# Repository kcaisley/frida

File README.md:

# FRIDA: Fast radiation imaging digitizer array

Frame-based radiation detectors with integrating front-ends are especially well-suited for applications like electron microscopy and X-ray imaging where hit-rates are high, spatial resolution should be maximized with simple pixels, and energy resolution is needed, but particles need not be individually discriminated in time, space, or spectrum. In an experimental setting, fast frame rates allow for real time in-situ observations. Potential subjects include rapid chemical processes, molecular dynamics of proteins, crystal nucleation and growth, material phase transitions, thermal conductivity, charge transfer, and mechanical strain.

This project pursues the possibility of a single-reticle array larger than 1 Mpixel with a continuous frame-rate surpassing 100,000 fps. For the conjunction of these two specifications to be met, one must have a compact and power efficient bank of column-parallel data converters, which at 10-12 bit resolution churn out data at a rate in excess of 1000 Gbps. To fit within the constraints of a chip bottom, the converter fabric must respect a restricted metric of 1 W/cm^2 while exceeding a 5 ksps/µm^2 sampling rate density. Successive-approximation ADCs are identified as the optimal choice, and various topologies and techniques will be analyzed to meet our goals.

Research question: How do we best allocate the quantity and weighting of SA bit positions, in order to yeild the highest resolution (in ENOB) for a given power, area, and power budget, and with a given amount of power supply noise?

## Block diagram of example system

## Modeling and analysis workflow

## Past designs vs current target

| Design                  | EDET DCD    | CoRDIA     | pre-Helena | Helena      |
|-------------------------|-------------|------------|------------|-------------|
| ADC resolution          | 8-bit       | 10-bit     | 8-bit      | 10-bit      |
| Conversion rate         | 10 MHz      | 2.5MHz     | 5 MHz      | 10 MHz      |
| Area of one ADC         | 100x200 μm² | 80x330 μm² | 60x800 μm² | 20x100 μm²  |
| Power of one ADC        | 1800 μW     | 30 μW      | 700 μW     | 100 μW      |
| FOM_csa (conv/sec/area) | 500 Hz/μm²  | 95 Hz/μm²  | 105 Hz/μm² | 5000 Hz/μm² |
| FOM_epc (energy/conv)   | 180 pJ      | 12 pJ      | 155 pJ     | 10 pJ       |
| FOM_ppa (power/area)    | 9.0 W/cm²   | 0.11 W/cm² | 1.45 W/cm² | 5.0 W/cm²   |
| ADC qty Mpix @ 100 KHz  | 10000       | 40000      | 20000      | 10000       |
| ADCs total pixel rate   | 100 Gpx/s   | 100 Gpx/s  | 100 Gpx/s  | 100 Gpx/s   |
| ADCs total data rate    | 800 Gb/s    | 1 Tb/s     | 800 Gb/s   | 1 Tb/s      |
| ADCs total area         | 2.0 cm²     | 10.5 cm²   | 9.6 cm²    | 0.2 cm²     |
| ADCs total power        | 35.0 W      | 1.2 W      | 14 W       | 1.0 W       |

NOTE: EDET DCD 1800 μW seems high, does it erroneously includes input amp?

# Project organization (proposal)

```
├── src
├── hdl
├── oa  (Caeleste input collateral eventually to be deleted)
├── netlists (library of generic netlists, and Verilog A models -> converted with find+replace)
├── impl
│   └── tsmc65 (1. impl netlists/oa schems/layouts/ 2. pointers to )
│   └── tsmc28
├── sim
│   └── tsmc65 (runs against impl netlists, since we have to have to include external libs)
│   └── tsmc28
├── tech
│   └── tsmc65 (EDA env start dir)
│   └── tsmc28
├── writing
```

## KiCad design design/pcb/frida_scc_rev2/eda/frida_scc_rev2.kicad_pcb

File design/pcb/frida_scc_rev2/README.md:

# frida_scc_rev2

The FRIDA single-chip card, revision 2.0: the test board for the FRIDA-1 ADC, written in
[Zener](https://docs.pcb.new/pages/spec.md). The `.zen` files are the source; the `pcb` tool makes
the netlist, the KiCad schematic and the KiCad board from them. The previous board is
`../frida-scc-1p1.kicad_pro`.

This is a first sketch: it builds (236 components) and generates. The board has frida-scc-1p1's
outline, stack-up and, for the 92 parts both boards have, its placement; the 144 new parts are
placed around them. Routing is in progress, nothing is simulated yet, and the items under "Open
questions" are undecided.

## Flow

```bash
# KiCad 10 for the pcb tool (the pinned AppImage, unpacked by tools/check.py install kicad)
export KICAD_APPDIR=$PWD/../../../build/tools/kicad-10.0.8/AppDir  # in the main checkout
export KICAD_CLI=$KICAD_APPDIR/bin/kicad-cli KICAD_PCBNEW=$KICAD_APPDIR/bin/pcbnew
export KICAD_PYTHON_INTERPRETER=$PWD/../kicad-python  # a wrapper that keeps pcb's PYTHONPATH

pcb build frida_scc_rev2.zen                       # check the design, write the netlist
pcb bom frida_scc_rev2.zen                         # the bill of materials, generics matched to parts
pcb apply schematic --no-open frida_scc_rev2.zen   # eda/frida_scc_rev2.kicad_sch and its pages
pcb layout --no-open frida_scc_rev2.zen            # eda/frida_scc_rev2.kicad_pcb
$KICAD_APPDIR/bin/python3.11 place_from_1p1.py    # frida-scc-1p1's outline and shared placement
$KICAD_APPDIR/bin/python3.11 place_new.py         # the new parts, around them
$KICAD_APPDIR/bin/python3.11 route_from_1p1.py    # frida-scc-1p1's tracks and ground plane for the shared parts
```

The board file owns the geometry (placement, routing, outline); later `pcb layout` runs keep it
and place only new parts, so the board and its project file in `eda/` are committed. The schematic is kept the same
way: the tool repairs only what no longer matches the design, and leaves the drawing alone.

`place_from_1p1.py` copies the outline and, for each part named in its table, the position,
rotation and side of the part it replaces on frida-scc-1p1 (the tap resistors sit on the pads of
the 1 kohm loads they replace). It also checks that the two boards' nets correspond one to one
over those parts, and moves every other part beside the outline. `place_new.py` then places
those: the supplies and the signal source left of the chip, the four probe channels and the
second RJ45 right of it, each small part beside the pin it serves. `route_from_1p1.py` copies frida-scc-1p1's tracks and vias onto the nets that are on the same
pads here, drops what a new part or a changed pad is in the way of, removes the loose ends that
led to parts that are gone, and gives the inner layers its ground plane: the LVDS pairs and the
analog input keep the routing that was measured. Run the three in this order to lay the board
out again from nothing.

Autorouting runs FreeRouting on this machine, driven directly (the `pcb` tool's own `route`
command was removed after release 0.4.60): KiCad writes the board as a Specctra design,
FreeRouting routes it, KiCad reads the result back. FreeRouting and its Java runtime are pinned
in `pyproject.toml` and fetched on first use.

```bash
uv run --no-project --python 3.12 python ../freeroute.py eda/frida_scc_rev2.kicad_pcb --minutes 30
```

## Schematic

Page 1 is frida-scc-1p1's sheet as it was drawn (its wires, notes and jumper pictures), with the
values and nets of this design; the parts that are new are on pages 2 to 5, in a block per
function, each pin with the tool's stub and net label (connections there are by net name, between
pages by global labels). `arrange_schematic.py` made it that way and says how in its heading; it
runs again when parts are added. `kicad-cli sch export pdf eda/frida_scc_rev2.kicad_sch` prints
all pages.

## Structure

| File | What it holds |
| --- | --- |
| `frida_scc_rev2.zen` | The board: rails, buses, one instance of each module, the probe matrix's node map |
| `modules/Asic.zen` | The FRIDA-1 die, its clock terminations, decoupling and reset pull-up |
| `modules/FpgaLink.zen` | DisplayPort (clocks, COMP_OUT) and RJ45 (SPI, reset) to the BDAQ53, the level shifter |
| `modules/AuxLink.zen` | A second RJ45: an SPI bus for the DAC and the probe matrix |
| `modules/InputAmp.zen` | SMAs, jumper network, THS4541, output filter, clamps |
| `modules/Supplies.zen` | +-5 V in; seven rails, each from its own regulator; external-rail jumpers |
| `modules/Regulator.zen`, `NegRegulator.zen` | One LT3045 or LT3094 rail |
| `modules/SignalSource.zen` | 2.5 V reference, 16-bit DAC, follower, two-pole filter |
| `modules/LvdsTap.zen` | One LVDS pair's resistive pick-off |
| `modules/ProbeChannel.zen` | One oscilloscope SMA: RF switch, slow multiplexer, select register |
| `components/` | Parts with their own symbol and footprint |

## What is new against frida-scc-1p1

**Supplies.** One raw +5 V and one raw -5 V come in on the Mini-Fit Jr. An LT3045 each makes
VDD_A, VDD_D, VDD_DAC and VDD_IO (1.2 V), 3.3 V for the analog parts and 2.5 V for the control
logic; an LT3094 makes -1 V. Each chip rail has a jumper that takes it from a lab supply
instead, as before. Each chip rail's regulator reports its load current (3 mV per mA) to the
probe matrix.

**Signal source.** An AD5541A 16-bit DAC on an ADR4525 2.5 V reference, a follower and a
145 kHz two-pole filter, with half the reference as the negative leg (+-1.25 V differential),
into the input network through jumpers beside the SMAs. It is for
ramps, DC levels and sines up to tens of kHz. Tones near the Nyquist frequency still come in on
the SMA.

**Probe matrix.** Four SMAs, one per oscilloscope channel. Each is switched by an ADG904
(DC-coupled, absorptive, 2 GHz) to one of three LVDS tap legs or to an 8:1 multiplexer of slow
nodes; four chained shift registers on the second RJ45 hold the selection. The taps replace the
1 kohm-to-ground resistors and the header pins that sat on the LVDS lines.

| Channel | Fast legs | Slow nodes (after the four chip rails) |
| --- | --- | --- |
| CH1 | INIT+, COMP_OUT-, SAMP- | VIN+, amplifier OUT+, source / 2, SPI_CS_B |
| CH2 | COMP+, INIT-, LOGIC- | VIN-, amplifier OUT-, VOCM, SPI_SCLK |
| CH3 | LOGIC+, COMP- | I(VDD_A), I(VDD_DAC), V3P3A / 2, SPI_SDI |
| CH4 | COMP_OUT+, SAMP+ | I(VDD_D), I(VDD_IO), (V3P3A + VS_N) / 2, SPI_SDO |

**Label.** The top silkscreen reads "FRIDA SCC / Rev 2.0" in the corner by mounting hole H4
(`place_new.py`'s `LABEL`; `place_new.py label` adds it to a board placed before it existed).

**Corrections.** The chip symbol's pin 13 is `COMP_OUT_N` (was spelled `COUP_OUT_N`); Q1 is a
BSS84 on a SOT-23 footprint the libraries resolve; the DisplayPort cable's power pin no longer
joins a supply rail. The RJ45 jack's footprint has the two plated holes its shield's solder
tabs need (frida-scc-1p1's had none), on the connectors' shell net.

**Kept.** The parts frida-scc-1p1 drew itself keep its symbols and footprints, and their 3-D
models are its files in `../frida.pretty`.

## Where the numbers come from

Read from the manufacturers' datasheets (copies in the main checkout's `build/datasheets`, not
committed): LT3045, LT3094, AD5541A, ADR4525, TMUX1108, ADG904. Several are older revisions from
distributor copies; check them against the current ones before ordering.

Not yet checked against a datasheet: the followers (OPA365), the select register (SN74LVC595A),
the THS4541's and BAV99's order codes.

## Open questions

- The second RJ45: which BDAQ53 port and FPGA pins it gets (or the PMOD header instead).
- The amplifier's positive supply: 3.3 V here (the negative one is frida-scc-1p1's -1 V); its
  bench value on frida-scc-1p1 is not recorded.
- The level shifter's direction straps: both groups are pulled to A-to-B on frida-scc-1p1, with
  SDO in the second group.
- The amplifier's output filter (499 ohm, 100 nF across: 1.6 kHz) passes ramps and DC but no
  sine test; fixed, or selectable?
- The COMP_OUT tap loads the chip's own driver (2.49 kohm per leg to ground when watched or not).
- The board thermistor's value.
- The six 47 uF bulk capacitors keep frida-scc-1p1's 0402 footprint, for which no part is found;
  what was fitted there?
- Not designed yet: a filtered square wave for tones near Nyquist, a fast step between two DAC
  levels, trimming the chip rails from the FPGA, a differential amplifier per SMA (each leg goes
  out single-ended), the stack-up.
- Not carried over from frida-scc-1p1 yet: its routing, ground pours, silkscreen labels and logos.

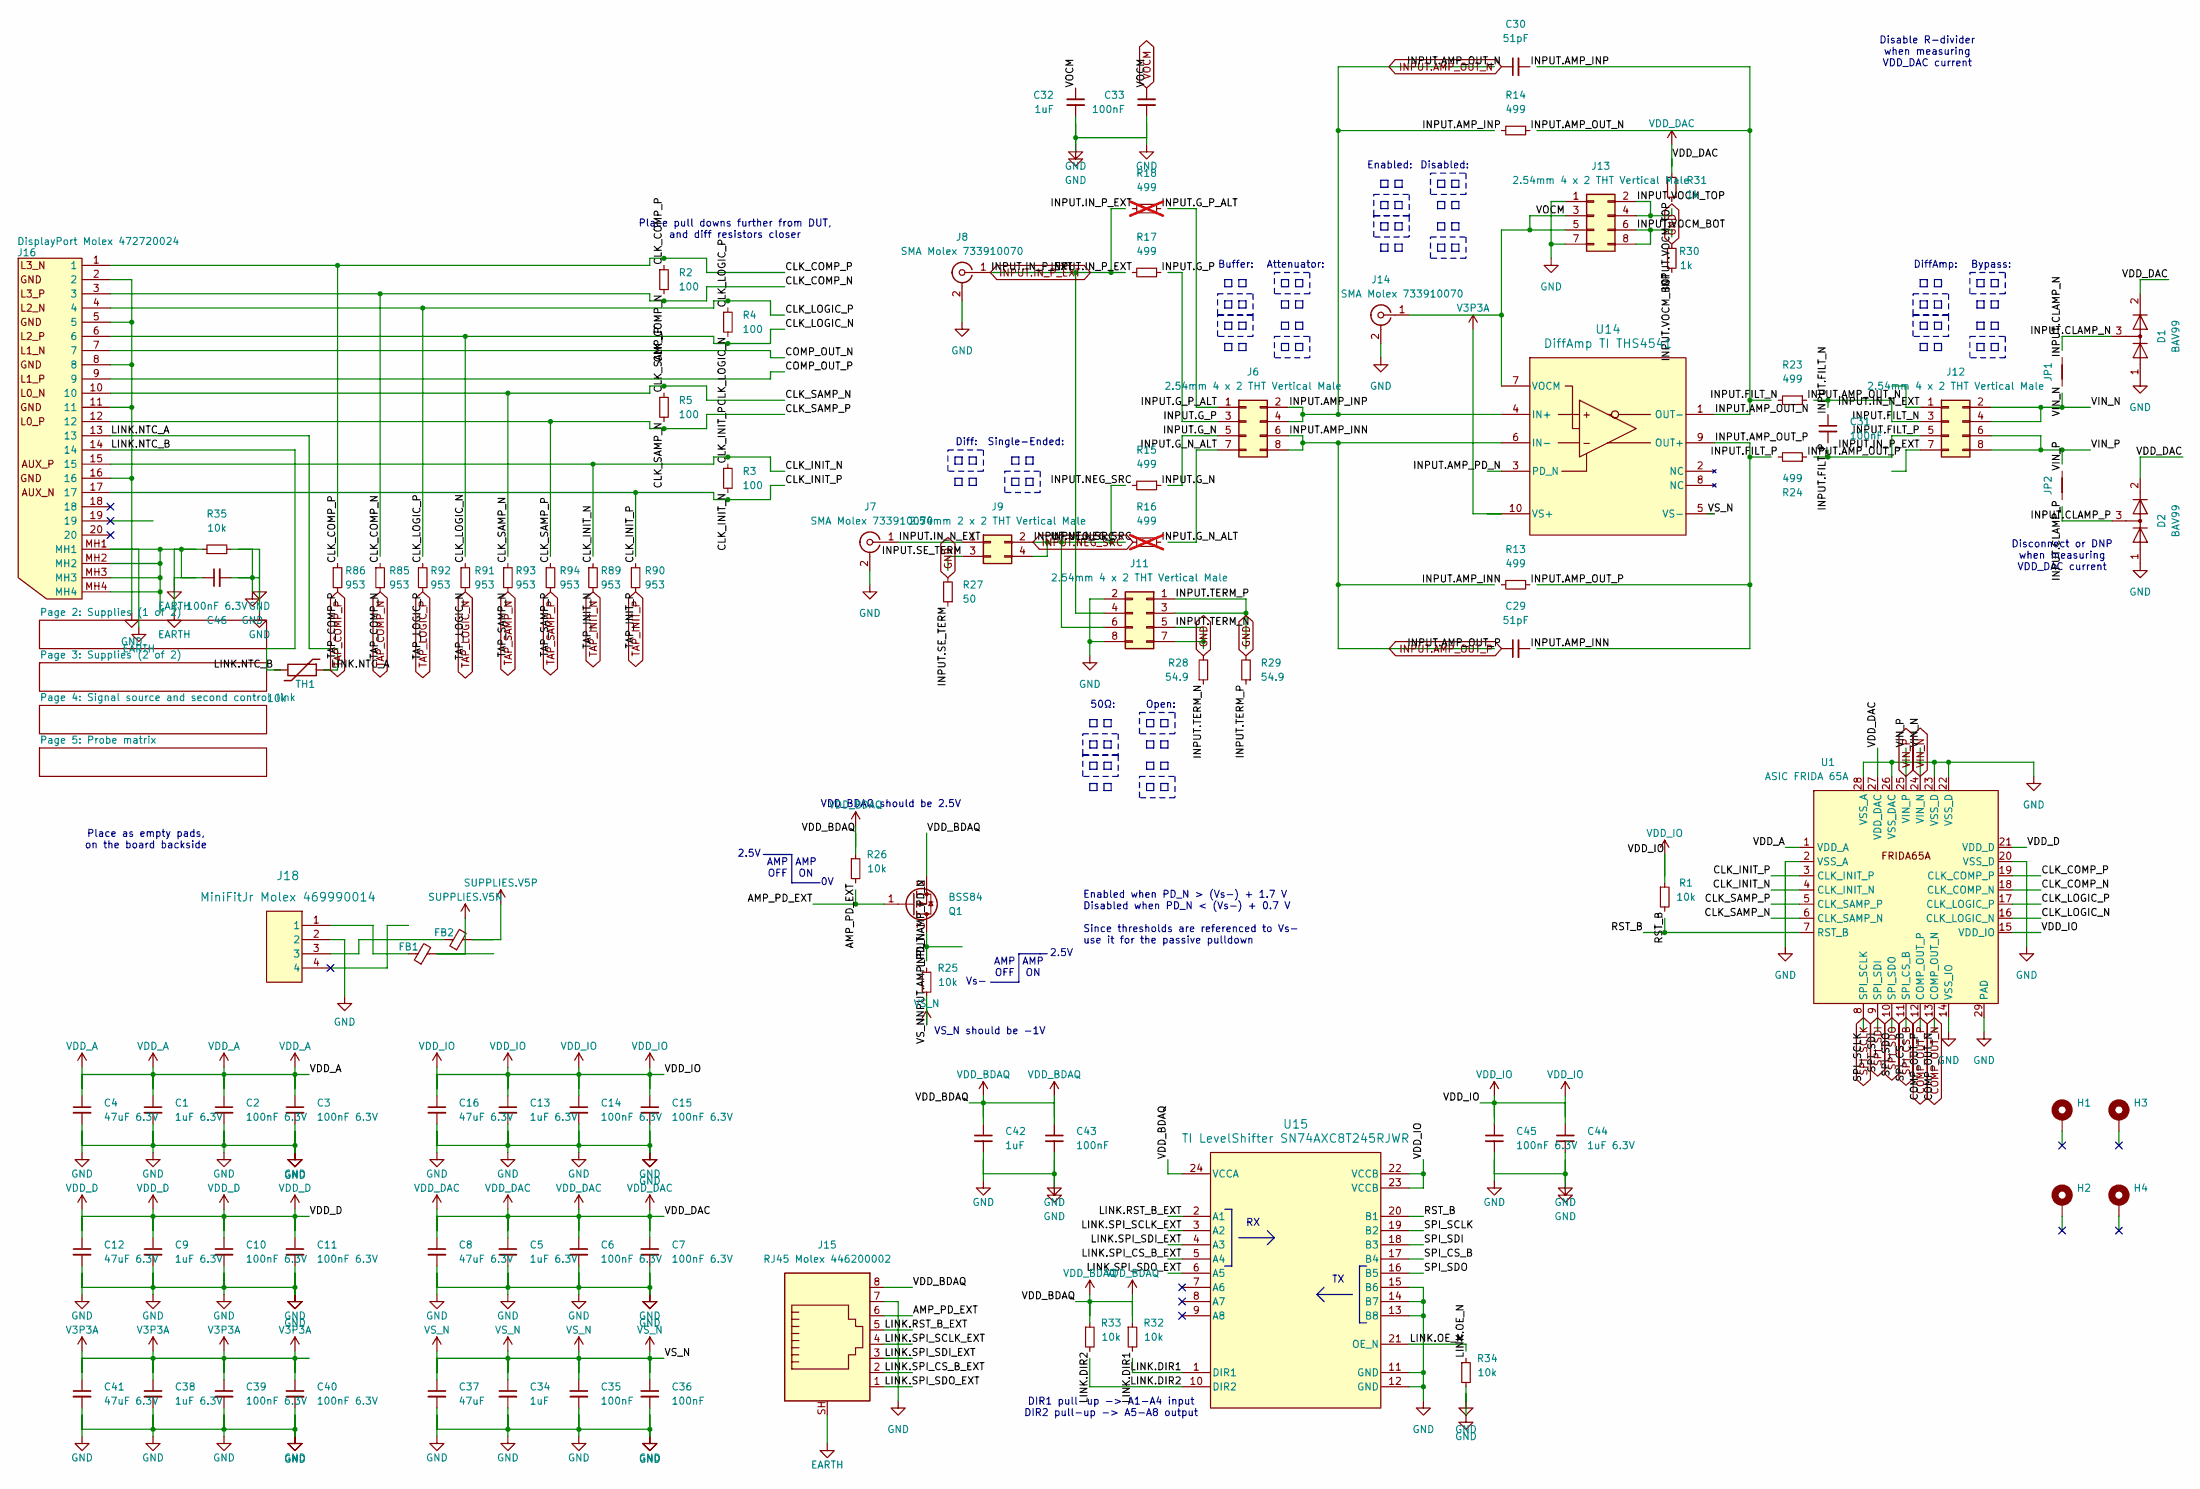
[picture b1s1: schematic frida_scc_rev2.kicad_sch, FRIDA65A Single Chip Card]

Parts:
C1, C5, C9, C13, C38, C44: 1uF 6.3V; C_0402_1005Metric
C2, C3, C6, C7, C10, C11, C14, C15, C39, C40, C45, C46: 100nF 6.3V; C_0402_1005Metric
C4, C8, C12, C16, C41: 47uF 6.3V; C_0402_1005Metric
C29, C30: 51pF; C_0402_1005Metric
C31, C33, C35, C36, C43: 100nF; C_0402_1005Metric
C32, C34, C42: 1uF; C_0402_1005Metric
C37: 47uF; C_0402_1005Metric
D1, D2: BAV99; SOT-23
FB1, FB2: 220 100MHz; R_0402_1005Metric
H1, H2, H3, H4: M3 DIN965 TopBottom; MountingHole_3.2mm_M3_DIN965_Pad_TopBottom
J6, J11, J12, J13: 2.54mm 4 x 2 THT Vertical Male; PinHeader_2x04_P2.54mm_Vertical
J7, J8, J14: SMA Molex 733910070; Molex_SMA_733910070
J9: 2.54mm 2 x 2 THT Vertical Male; PinHeader_2x02_P2.54mm_Vertical
J15: RJ45 Molex 446200002; Molex_RJ45_446200002
J16: DisplayPort Molex 472720024; Molex_DisplayPort_472720024; Manufacturer_Part_Number 47272-0024; Mouser Part Number 538-47272-0024
J18: MiniFitJr Molex 469990014; Molex_MiniFitJr_469990014
JP1, JP2: SolderJumper-2_P1.3mm_Open_Pad1.0x1.5mm
Q1: BSS84; SOT-23
R1, R25, R26, R32, R33, R34, R35: 10k; R_0402_1005Metric
R2, R3, R4, R5: 100; R_0402_1005Metric
R13, R14, R15, R17, R23, R24: 499; R_0402_1005Metric
R16, R18: 499; R_0402_1005Metric; not fitted
R27: 50; R_0402_1005Metric
R28, R29: 54.9; R_0402_1005Metric
R30, R31: 1k; R_0402_1005Metric
R85, R86, R89, R90, R91, R92, R93, R94: 953; R_0402_1005Metric
TH1: 10k; R_0402_1005Metric
U1: ASIC FRIDA 65A; FRIDA_ASIC_Pad
U14: DiffAmp TI THS4541; TI_DiffAmp_THS4541
U15: TI LevelShifter SN74AXC8T245RJWR; TI_LevelShifter_SN74AXC8T245RJWR

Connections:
AMP_PD_EXT: J15.6, Q1.1 (K), R26.2
CLK_COMP_N: J16.3, R2.2, R85.1, U1.18 (CLK_COMP_N)
CLK_COMP_P: J16.1, R2.1, R86.1, U1.19 (CLK_COMP_P)
CLK_INIT_N: J16.15, R3.2, R89.1, U1.4 (CLK_INIT_N)
CLK_INIT_P: J16.17, R3.1, R90.1, U1.3 (CLK_INIT_P)
CLK_LOGIC_N: J16.6, R4.2, R91.1, U1.16 (CLK_LOGIC_N)
CLK_LOGIC_P: J16.4, R4.1, R92.1, U1.17 (CLK_LOGIC_P)
CLK_SAMP_N: J16.10, R5.2, R93.1, U1.6 (CLK_SAMP_N)
CLK_SAMP_P: J16.12, R5.1, R94.1, U1.5 (CLK_SAMP_P)
COMP_OUT_N: J16.7, U1.13 (COMP_OUT_N); also elsewhere on the board
COMP_OUT_P: J16.9, U1.12 (COMP_OUT_P); also elsewhere on the board
EARTH: C46.1, J15.SH, J16.MH1, J16.MH2, J16.MH3, J16.MH4, R35.1; also elsewhere on the board
GND: C1.2, C2.2, C3.2, C4.2, C5.2, C6.2, C7.2, C8.2, C9.2, C10.2, C11.2, C12.2, C13.2, C14.2, C15.2, C16.2, C32.2, C33.2, C34.2, C35.2, C36.2, C37.2, C38.2, C39.2, C40.2, C41.2, C42.2, C43.2, C44.2, C45.2, C46.2, D1.1 (K), D2.1 (K), J7.2 (Ext), J8.2 (Ext), J11.2, J11.8, J13.1, J13.7, J14.2 (Ext), J15.7, J16.2, J16.5, J16.8, J16.11, J16.16, J18.2, R27.2, R28.2, R29.2, R30.2, R34.2, R35.2, U1.2 (VSS_A), U1.14 (VSS_IO), U1.20 (VSS_D), U1.22 (VSS_D), U1.23 (VSS_D), U1.26 (VSS_DAC), U1.28 (VSS_A), U1.29 (PAD), U15.11 (GND), U15.12 (GND), U15.13 (B8), U15.14 (B7), U15.15 (B6); also elsewhere on the board
H1.P1: H1.1
H2.P1: H2.1
H3.P1: H3.1
H4.P1: H4.1
INPUT.AMP_INN: C29.2, J6.6, J6.8, R13.2, U14.6 (IN-)
INPUT.AMP_INP: C30.2, J6.2, J6.4, R14.2, U14.4 (IN+)
INPUT.AMP_OUT_N: C30.1, R14.1, R23.1, U14.1 (OUT-); also elsewhere on the board
INPUT.AMP_OUT_P: C29.1, R13.1, R24.1, U14.9 (OUT+); also elsewhere on the board
INPUT.AMP_PD_N: Q1.3 (K), R25.1, U14.3 (PD_N)
INPUT.CLAMP_N: D1.3 (K), JP1.1
INPUT.CLAMP_P: D2.3 (K), JP2.2
INPUT.FILT_N: C31.1, J12.3, R23.2
INPUT.FILT_P: C31.2, J12.5, R24.2
INPUT.G_N: J6.5, R15.1
INPUT.G_N_ALT: J6.7, R16.1
INPUT.G_P: J6.3, R17.1
INPUT.G_P_ALT: J6.1, R18.1
INPUT.IN_N_EXT: J7.1 (In), J9.1, J12.1
INPUT.IN_P_EXT: J8.1 (In), J11.4, J12.7, R17.2, R18.2; also elsewhere on the board
INPUT.NEG_SRC: J9.2, J9.4, J11.6, R15.2, R16.2; also elsewhere on the board
INPUT.SE_TERM: J9.3, R27.1
INPUT.TERM_N: J11.5, J11.7, R28.1
INPUT.TERM_P: J11.1, J11.3, R29.1
INPUT.VOCM_BOT: J13.6, J13.8, R30.1
INPUT.VOCM_TOP: J13.2, J13.4, R31.1
LINK.DIR1: R32.2, U15.1 (DIR1)
LINK.DIR2: R33.2, U15.10 (DIR2)
LINK.J_DP.NC_DisplayPort_Molex_472720024_18: J16.18
LINK.J_DP.NC_DisplayPort_Molex_472720024_19: J16.19
LINK.J_DP.NC_DisplayPort_Molex_472720024_20: J16.20
LINK.NTC_A: J16.13, TH1.1
LINK.NTC_B: J16.14, TH1.2
LINK.OE_N: R34.1, U15.21 (OE_N)
LINK.RST_B_EXT: J15.5, U15.2 (A1)
LINK.SPI_CS_B_EXT: J15.2, U15.5 (A4)
LINK.SPI_SCLK_EXT: J15.4, U15.3 (A2)
LINK.SPI_SDI_EXT: J15.3, U15.4 (A3)
LINK.SPI_SDO_EXT: J15.1, U15.6 (A5)
LINK.U_SHIFT.NC_TI_LevelShifter_SN74AXC8T245RJWR_A6: U15.7 (A6)
LINK.U_SHIFT.NC_TI_LevelShifter_SN74AXC8T245RJWR_A7: U15.8 (A7)
LINK.U_SHIFT.NC_TI_LevelShifter_SN74AXC8T245RJWR_A8: U15.9 (A8)
RST_B: R1.2, U1.7 (RST_B), U15.20 (B1)
SPI_CS_B: U1.11 (SPI_CS_B), U15.17 (B4); also elsewhere on the board
SPI_SCLK: U1.8 (SPI_SCLK), U15.19 (B2); also elsewhere on the board
SPI_SDI: U1.9 (SPI_SDI), U15.18 (B3); also elsewhere on the board
SPI_SDO: U1.10 (SPI_SDO), U15.16 (B5); also elsewhere on the board
SUPPLIES.J_PWR.NC_MiniFitJr_Molex_469990014_4: J18.4
SUPPLIES.V5N: FB1.2; also elsewhere on the board
SUPPLIES.V5N_RAW: FB1.1, J18.1
SUPPLIES.V5P: FB2.2; also elsewhere on the board
SUPPLIES.V5P_RAW: FB2.1, J18.3
TAP_COMP_N: R85.2; also elsewhere on the board
TAP_COMP_P: R86.2; also elsewhere on the board
TAP_INIT_N: R89.2; also elsewhere on the board
TAP_INIT_P: R90.2; also elsewhere on the board
TAP_LOGIC_N: R91.2; also elsewhere on the board
TAP_LOGIC_P: R92.2; also elsewhere on the board
TAP_SAMP_N: R93.2; also elsewhere on the board
TAP_SAMP_P: R94.2; also elsewhere on the board
V3P3A: C38.1, C39.1, C40.1, C41.1, U14.10 (VS+); also elsewhere on the board
VDD_A: C1.1, C2.1, C3.1, C4.1, U1.1 (VDD_A); also elsewhere on the board
VDD_BDAQ: C42.1, C43.1, J15.8, Q1.2 (A), R26.1, R32.1, R33.1, U15.24 (VCCA)
VDD_D: C9.1, C10.1, C11.1, C12.1, U1.21 (VDD_D); also elsewhere on the board
VDD_DAC: C5.1, C6.1, C7.1, C8.1, D1.2 (A), D2.2 (A), R31.2, U1.27 (VDD_DAC); also elsewhere on the board
VDD_IO: C13.1, C14.1, C15.1, C16.1, C44.1, C45.1, R1.1, U1.15 (VDD_IO), U15.22 (VCCB), U15.23 (VCCB); also elsewhere on the board
VIN_N: J12.2, J12.4, JP1.2, U1.24 (VIN_N); also elsewhere on the board
VIN_P: J12.6, J12.8, JP2.1, U1.25 (VIN_P); also elsewhere on the board
VOCM: C32.1, C33.1, J13.3, J13.5, J14.1 (In), U14.7 (VOCM); also elsewhere on the board
VS_N: C34.1, C35.1, C36.1, C37.1, R25.2, U14.5 (VS-); also elsewhere on the board

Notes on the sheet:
2.5V
Vs-
Bypass:
DiffAmp:
Single-Ended:
Disable R-divider when measuring VDD_DAC current
AMP ON
Disconnect or DNP when measuring VDD_DAC current
Enabled when PD_N > (Vs-) + 1.7 V Disabled when PD_N < (Vs-) + 0.7 V Since thresholds are referenced to Vs- use it for the passive pulldown
Open:
Attenuator:
Place as empty pads, on the board backside
DIR1 pull-up -> A1-A4 input DIR2 pull-up -> A5-A8 output
50Ω:
Enabled:
VDD_BDAQ should be 2.5V
Diff:
Place pull downs further from DUT, and diff resistors closer
VS_N should be -1V
AMP OFF
Disabled:
Buffer:

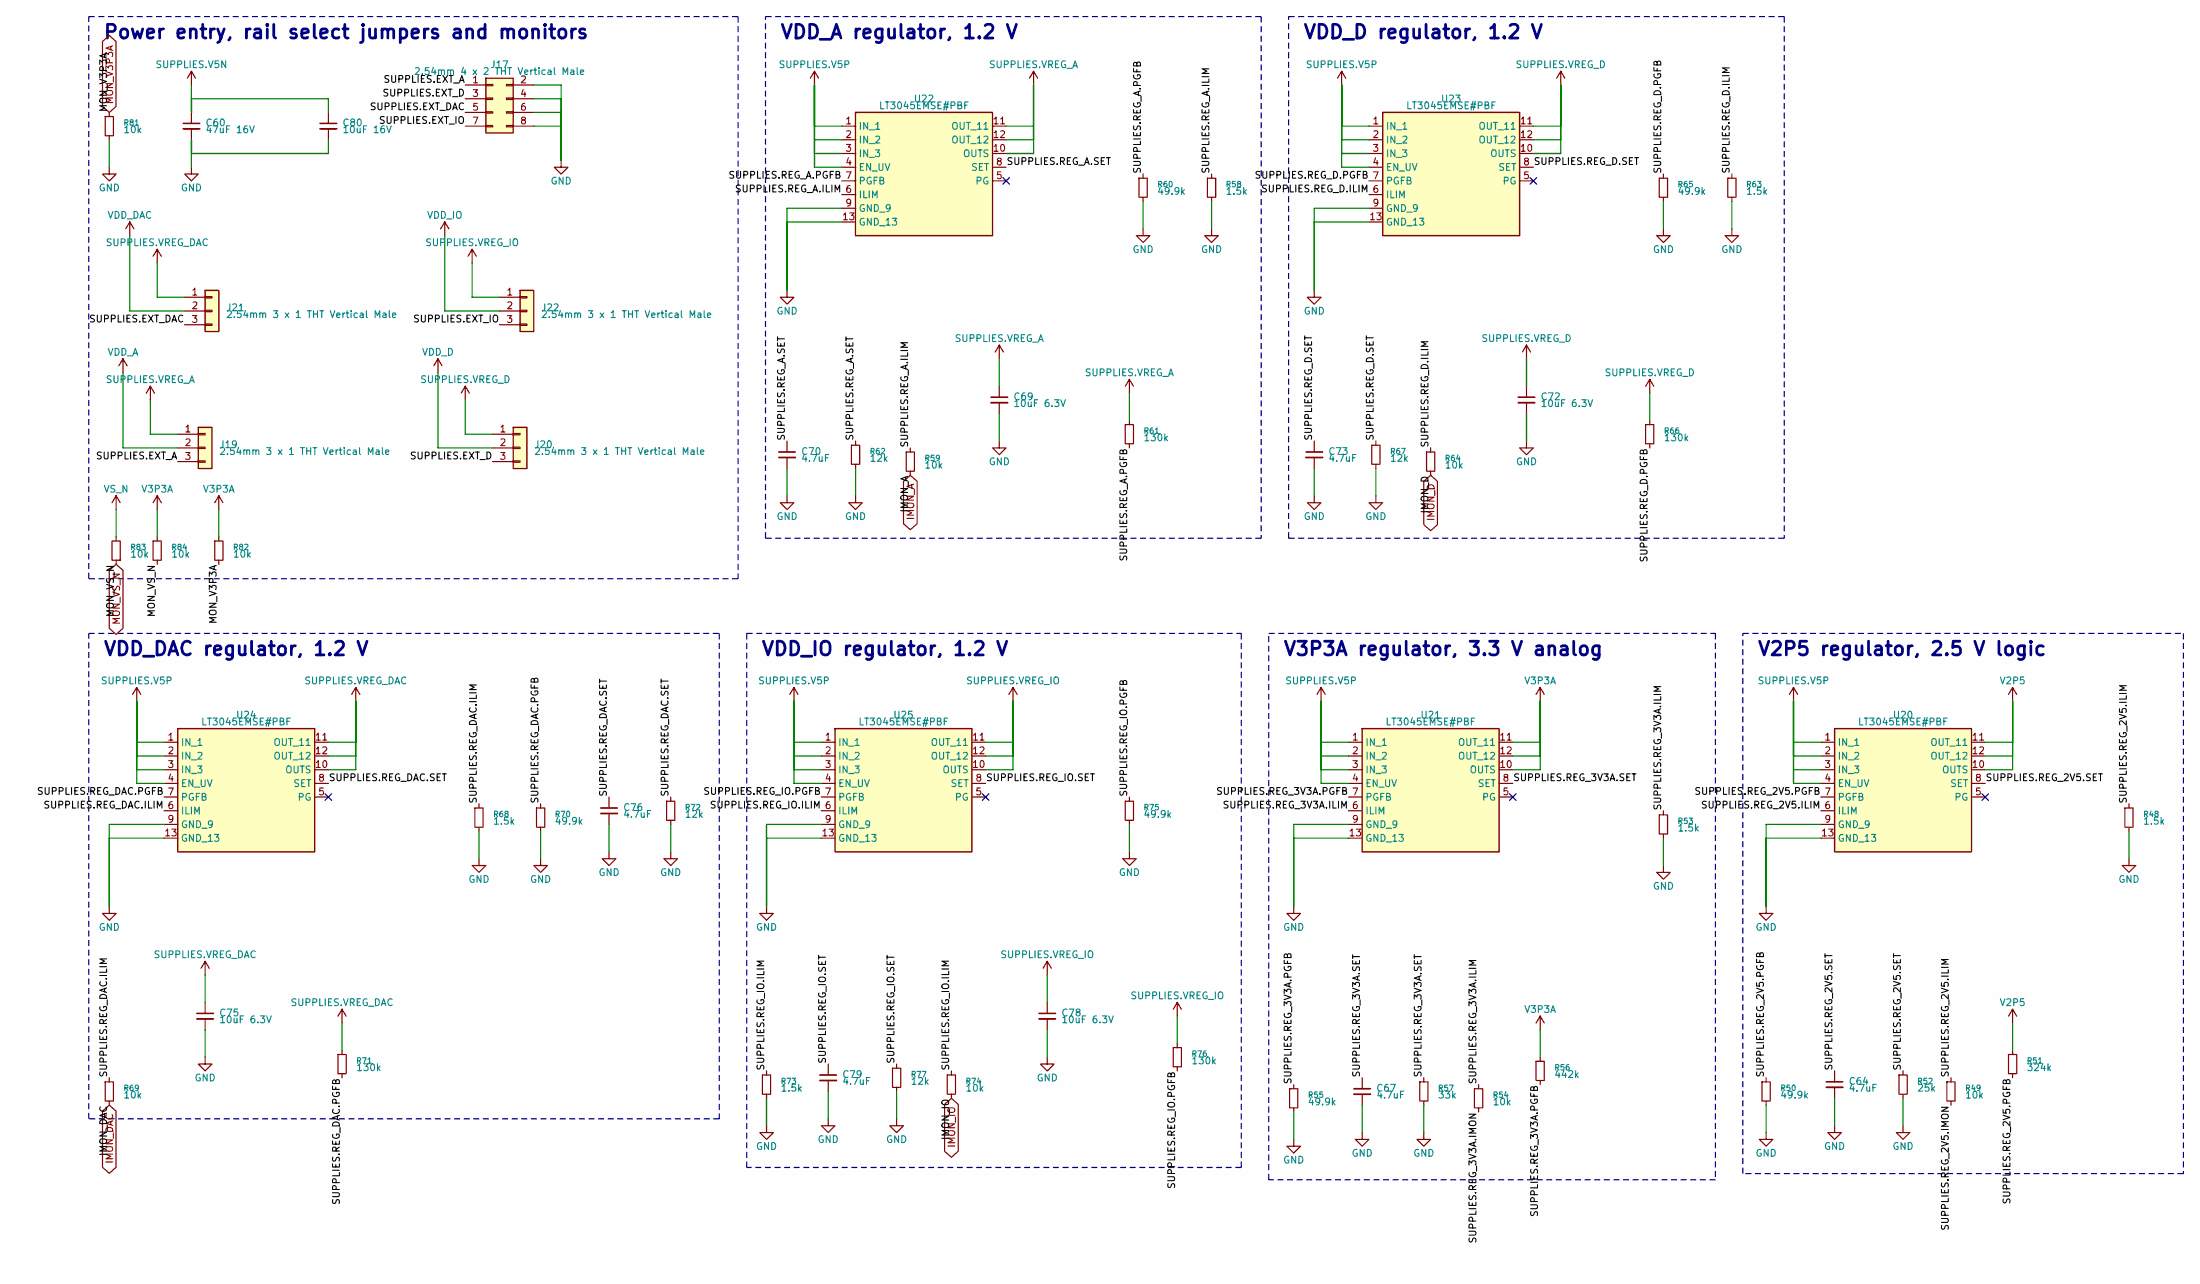
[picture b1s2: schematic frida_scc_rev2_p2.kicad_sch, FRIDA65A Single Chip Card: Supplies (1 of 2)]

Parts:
C60: 47uF 16V; C_1210_3225Metric
C64, C67, C70, C73, C76, C79: 4.7uF; C_0603_1608Metric
C69, C72, C75, C78: 10uF 6.3V; C_0805_2012Metric
C80: 10uF 16V; C_0805_2012Metric
J17: 2.54mm 4 x 2 THT Vertical Male; PinHeader_2x04_P2.54mm_Vertical
J19, J20, J21, J22: 2.54mm 3 x 1 THT Vertical Male; PinHeader_1x03_P2.54mm_Vertical
R48, R53, R58, R63, R68, R73: 1.5k; R_0402_1005Metric
R49, R54, R59, R64, R69, R74, R81, R82, R83, R84: 10k; R_0402_1005Metric
R50, R55, R60, R65, R70, R75: 49.9k; R_0402_1005Metric
R51: 324k; R_0402_1005Metric
R52: 25k; R_0603_1608Metric
R56: 442k; R_0402_1005Metric
R57: 33k; R_0603_1608Metric
R61, R66, R71, R76: 130k; R_0402_1005Metric
R62, R67, R72, R77: 12k; R_0603_1608Metric
U20, U21, U22, U23, U24, U25: LT3045EMSE#PBF; MSOP-12-1EP_3x4.039mm_P0.65mm_EP1.651x2.845mm

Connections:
GND: C60.2, C64.2, C67.2, C69.2, C70.2, C72.2, C73.2, C75.2, C76.2, C78.2, C79.2, C80.2, J17.2, J17.4, J17.6, J17.8, R48.2, R50.2, R52.2, R53.2, R55.2, R57.2, R58.2, R60.2, R62.2, R63.2, R65.2, R67.2, R68.2, R70.2, R72.2, R73.2, R75.2, R77.2, R81.2, U20.9 (GND_9), U20.13 (GND_13), U21.9 (GND_9), U21.13 (GND_13), U22.9 (GND_9), U22.13 (GND_13), U23.9 (GND_9), U23.13 (GND_13), U24.9 (GND_9), U24.13 (GND_13), U25.9 (GND_9), U25.13 (GND_13); also elsewhere on the board
IMON_A: R59.2; also elsewhere on the board
IMON_D: R64.2; also elsewhere on the board
IMON_DAC: R69.2; also elsewhere on the board
IMON_IO: R74.2; also elsewhere on the board
MON_V3P3A: R81.1, R82.2; also elsewhere on the board
MON_VS_N: R83.1, R84.2; also elsewhere on the board
SUPPLIES.EXT_A: J17.1, J19.3
SUPPLIES.EXT_D: J17.3, J20.3
SUPPLIES.EXT_DAC: J17.5, J21.3
SUPPLIES.EXT_IO: J17.7, J22.3
SUPPLIES.REG_2V5.ILIM: R48.1, R49.1, U20.6 (ILIM)
SUPPLIES.REG_2V5.IMON: R49.2
SUPPLIES.REG_2V5.PGFB: R50.1, R51.2, U20.7 (PGFB)
SUPPLIES.REG_2V5.SET: C64.1, R52.1, U20.8 (SET)
SUPPLIES.REG_2V5.U_REG.NC_LT3045_PG: U20.5 (PG)
SUPPLIES.REG_3V3A.ILIM: R53.1, R54.1, U21.6 (ILIM)
SUPPLIES.REG_3V3A.IMON: R54.2
SUPPLIES.REG_3V3A.PGFB: R55.1, R56.2, U21.7 (PGFB)
SUPPLIES.REG_3V3A.SET: C67.1, R57.1, U21.8 (SET)
SUPPLIES.REG_3V3A.U_REG.NC_LT3045_PG: U21.5 (PG)
SUPPLIES.REG_A.ILIM: R58.1, R59.1, U22.6 (ILIM)
SUPPLIES.REG_A.PGFB: R60.1, R61.2, U22.7 (PGFB)
SUPPLIES.REG_A.SET: C70.1, R62.1, U22.8 (SET)
SUPPLIES.REG_A.U_REG.NC_LT3045_PG: U22.5 (PG)
SUPPLIES.REG_D.ILIM: R63.1, R64.1, U23.6 (ILIM)
SUPPLIES.REG_D.PGFB: R65.1, R66.2, U23.7 (PGFB)
SUPPLIES.REG_D.SET: C73.1, R67.1, U23.8 (SET)
SUPPLIES.REG_D.U_REG.NC_LT3045_PG: U23.5 (PG)
SUPPLIES.REG_DAC.ILIM: R68.1, R69.1, U24.6 (ILIM)
SUPPLIES.REG_DAC.PGFB: R70.1, R71.2, U24.7 (PGFB)
SUPPLIES.REG_DAC.SET: C76.1, R72.1, U24.8 (SET)
SUPPLIES.REG_DAC.U_REG.NC_LT3045_PG: U24.5 (PG)
SUPPLIES.REG_IO.ILIM: R73.1, R74.1, U25.6 (ILIM)
SUPPLIES.REG_IO.PGFB: R75.1, R76.2, U25.7 (PGFB)
SUPPLIES.REG_IO.SET: C79.1, R77.1, U25.8 (SET)
SUPPLIES.REG_IO.U_REG.NC_LT3045_PG: U25.5 (PG)
SUPPLIES.V5N: C60.1, C80.1; also elsewhere on the board
SUPPLIES.V5P: U20.1 (IN_1), U20.2 (IN_2), U20.3 (IN_3), U20.4 (EN_UV), U21.1 (IN_1), U21.2 (IN_2), U21.3 (IN_3), U21.4 (EN_UV), U22.1 (IN_1), U22.2 (IN_2), U22.3 (IN_3), U22.4 (EN_UV), U23.1 (IN_1), U23.2 (IN_2), U23.3 (IN_3), U23.4 (EN_UV), U24.1 (IN_1), U24.2 (IN_2), U24.3 (IN_3), U24.4 (EN_UV), U25.1 (IN_1), U25.2 (IN_2), U25.3 (IN_3), U25.4 (EN_UV); also elsewhere on the board
SUPPLIES.VREG_A: C69.1, J19.1, R61.1, U22.10 (OUTS), U22.11 (OUT_11), U22.12 (OUT_12)
SUPPLIES.VREG_D: C72.1, J20.1, R66.1, U23.10 (OUTS), U23.11 (OUT_11), U23.12 (OUT_12)
SUPPLIES.VREG_DAC: C75.1, J21.1, R71.1, U24.10 (OUTS), U24.11 (OUT_11), U24.12 (OUT_12)
SUPPLIES.VREG_IO: C78.1, J22.1, R76.1, U25.10 (OUTS), U25.11 (OUT_11), U25.12 (OUT_12)
V2P5: R51.1, U20.10 (OUTS), U20.11 (OUT_11), U20.12 (OUT_12); also elsewhere on the board
V3P3A: R56.1, R82.1, R84.1, U21.10 (OUTS), U21.11 (OUT_11), U21.12 (OUT_12); also elsewhere on the board
VDD_A: J19.2; also elsewhere on the board
VDD_D: J20.2; also elsewhere on the board
VDD_DAC: J21.2; also elsewhere on the board
VDD_IO: J22.2; also elsewhere on the board
VS_N: R83.2; also elsewhere on the board

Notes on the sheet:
Power entry, rail select jumpers and monitors
VDD_A regulator, 1.2 V
VDD_D regulator, 1.2 V
VDD_DAC regulator, 1.2 V
VDD_IO regulator, 1.2 V
V3P3A regulator, 3.3 V analog
V2P5 regulator, 2.5 V logic

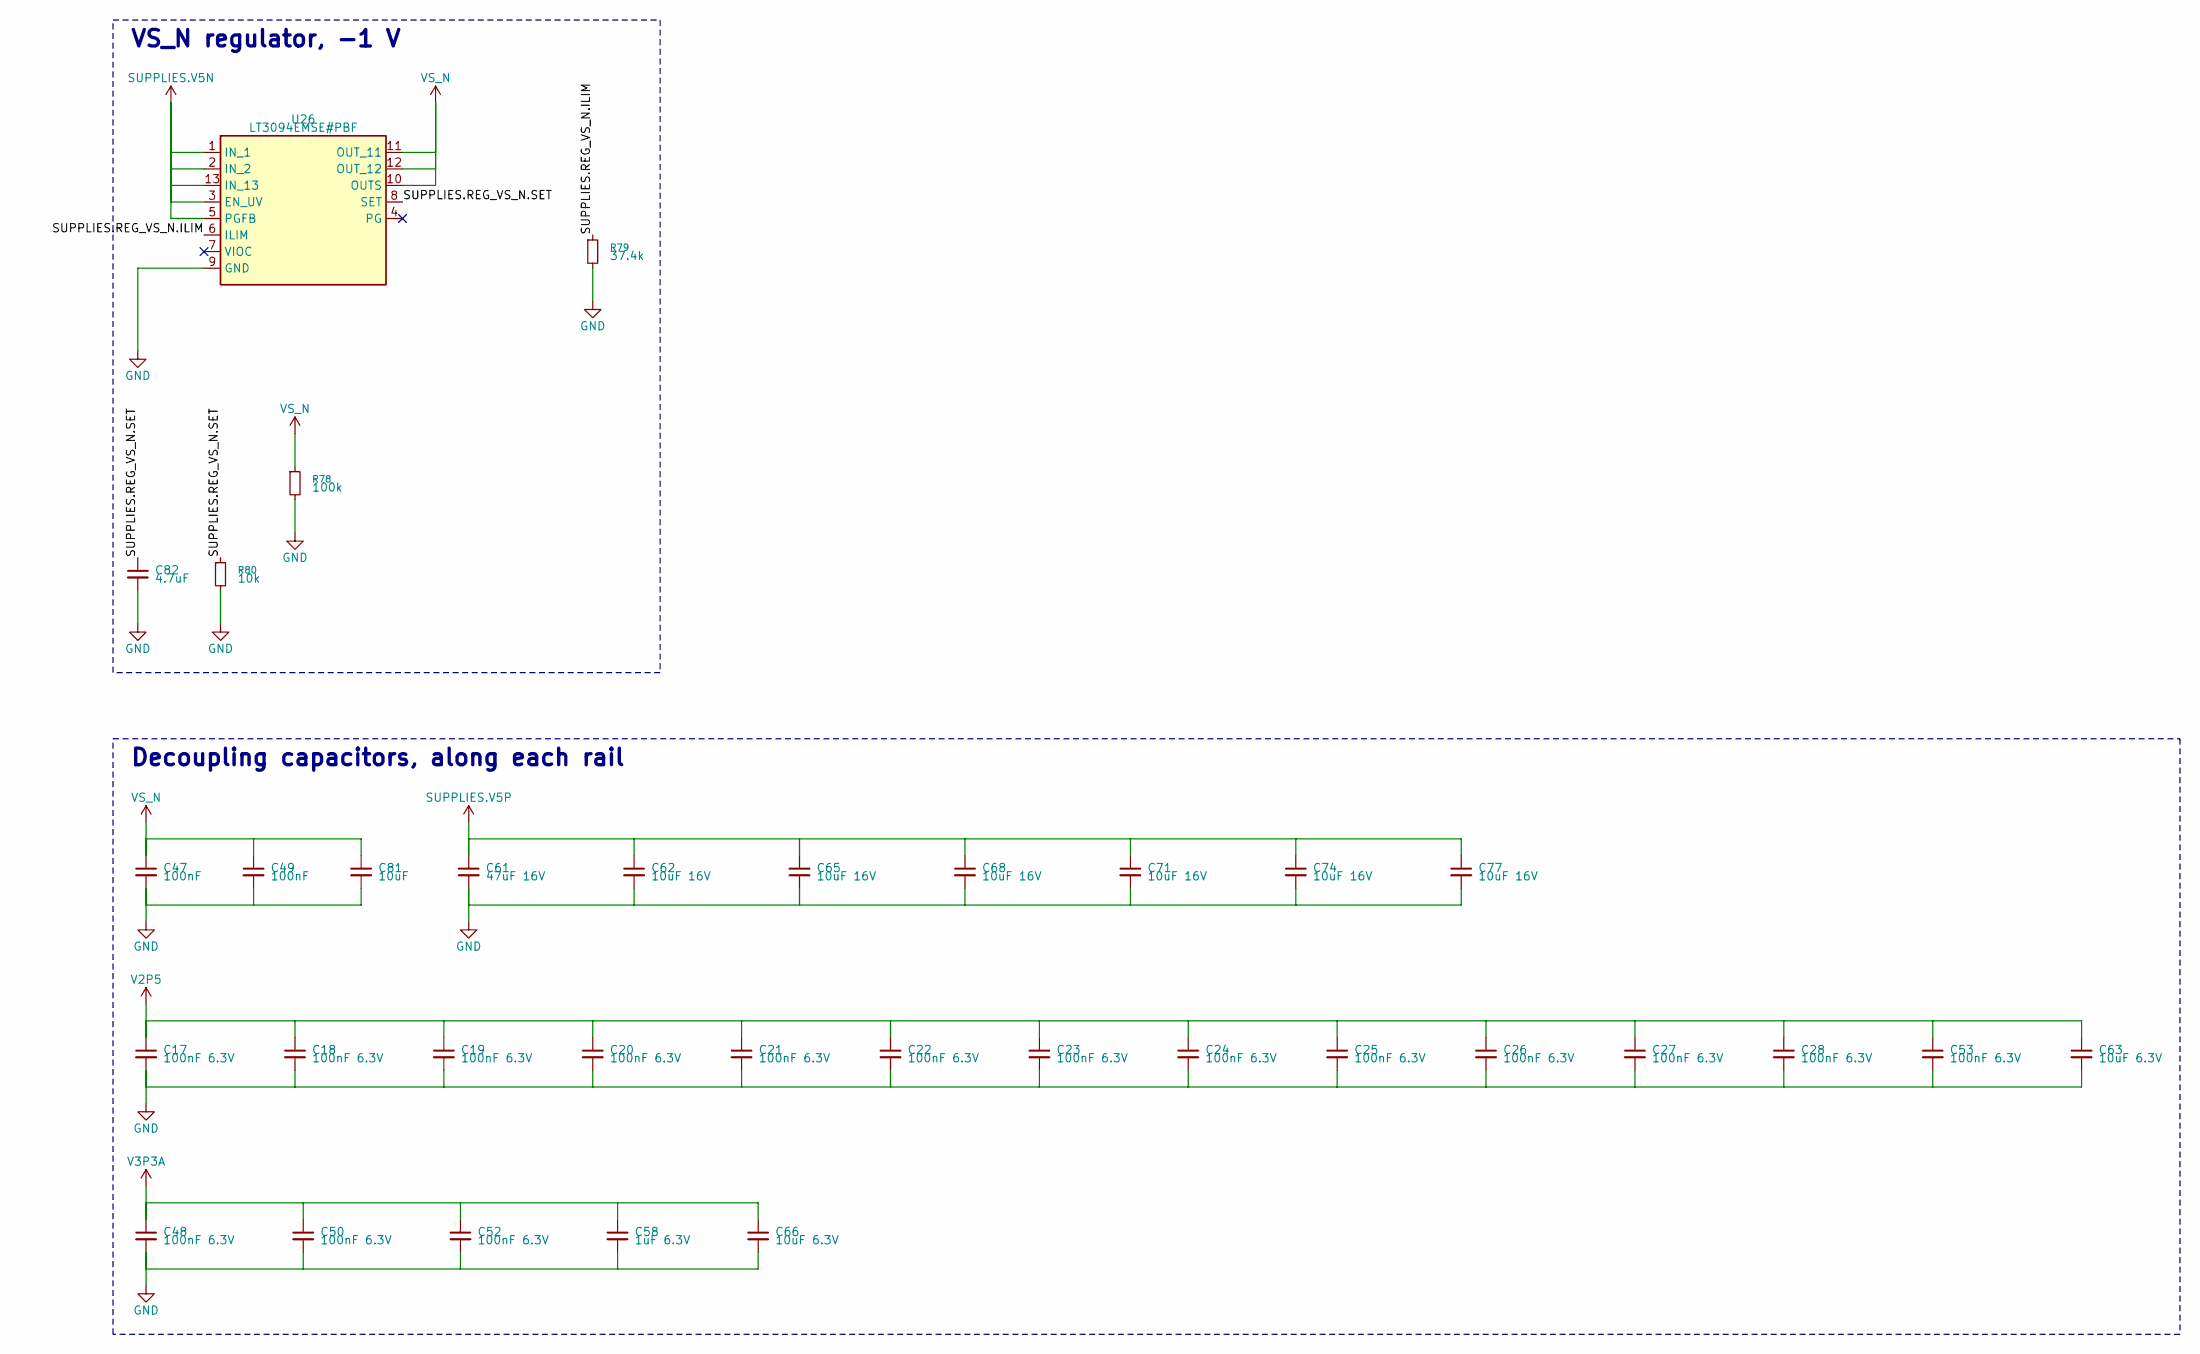
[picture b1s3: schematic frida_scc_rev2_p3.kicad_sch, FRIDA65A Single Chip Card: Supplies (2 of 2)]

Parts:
C17, C18, C19, C20, C21, C22, C23, C24, C25, C26, C27, C28, C48, C50, C52, C53: 100nF 6.3V; C_0402_1005Metric
C47, C49: 100nF; C_0402_1005Metric
C58: 1uF 6.3V; C_0402_1005Metric
C61: 47uF 16V; C_1210_3225Metric
C62, C65, C68, C71, C74, C77: 10uF 16V; C_0805_2012Metric
C63, C66: 10uF 6.3V; C_0805_2012Metric
C81: 10uF; C_0805_2012Metric
C82: 4.7uF; C_0603_1608Metric
R78: 100k; R_0402_1005Metric
R79: 37.4k; R_0402_1005Metric
R80: 10k; R_0603_1608Metric
U26: LT3094EMSE#PBF; MSOP-12-1EP_3x4.039mm_P0.65mm_EP1.651x2.845mm

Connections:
GND: C17.2, C18.2, C19.2, C20.2, C21.2, C22.2, C23.2, C24.2, C25.2, C26.2, C27.2, C28.2, C47.2, C48.2, C49.2, C50.2, C52.2, C53.2, C58.2, C61.2, C62.2, C63.2, C65.2, C66.2, C68.2, C71.2, C74.2, C77.2, C81.2, C82.2, R78.2, R79.2, R80.2, U26.9 (GND); also elsewhere on the board
SUPPLIES.REG_VS_N.ILIM: R79.1, U26.6 (ILIM)
SUPPLIES.REG_VS_N.SET: C82.1, R80.1, U26.8 (SET)
SUPPLIES.REG_VS_N.U_REG.NC_LT3094_PG: U26.4 (PG)
SUPPLIES.REG_VS_N.U_REG.NC_LT3094_VIOC: U26.7 (VIOC)
SUPPLIES.V5N: U26.1 (IN_1), U26.2 (IN_2), U26.3 (EN_UV), U26.5 (PGFB), U26.13 (IN_13); also elsewhere on the board
SUPPLIES.V5P: C61.1, C62.1, C65.1, C68.1, C71.1, C74.1, C77.1; also elsewhere on the board
V2P5: C17.1, C18.1, C19.1, C20.1, C21.1, C22.1, C23.1, C24.1, C25.1, C26.1, C27.1, C28.1, C53.1, C63.1; also elsewhere on the board
V3P3A: C48.1, C50.1, C52.1, C58.1, C66.1; also elsewhere on the board
VS_N: C47.1, C49.1, C81.1, R78.1, U26.10 (OUTS), U26.11 (OUT_11), U26.12 (OUT_12); also elsewhere on the board

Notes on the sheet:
VS_N regulator, -1 V
Decoupling capacitors, along each rail
